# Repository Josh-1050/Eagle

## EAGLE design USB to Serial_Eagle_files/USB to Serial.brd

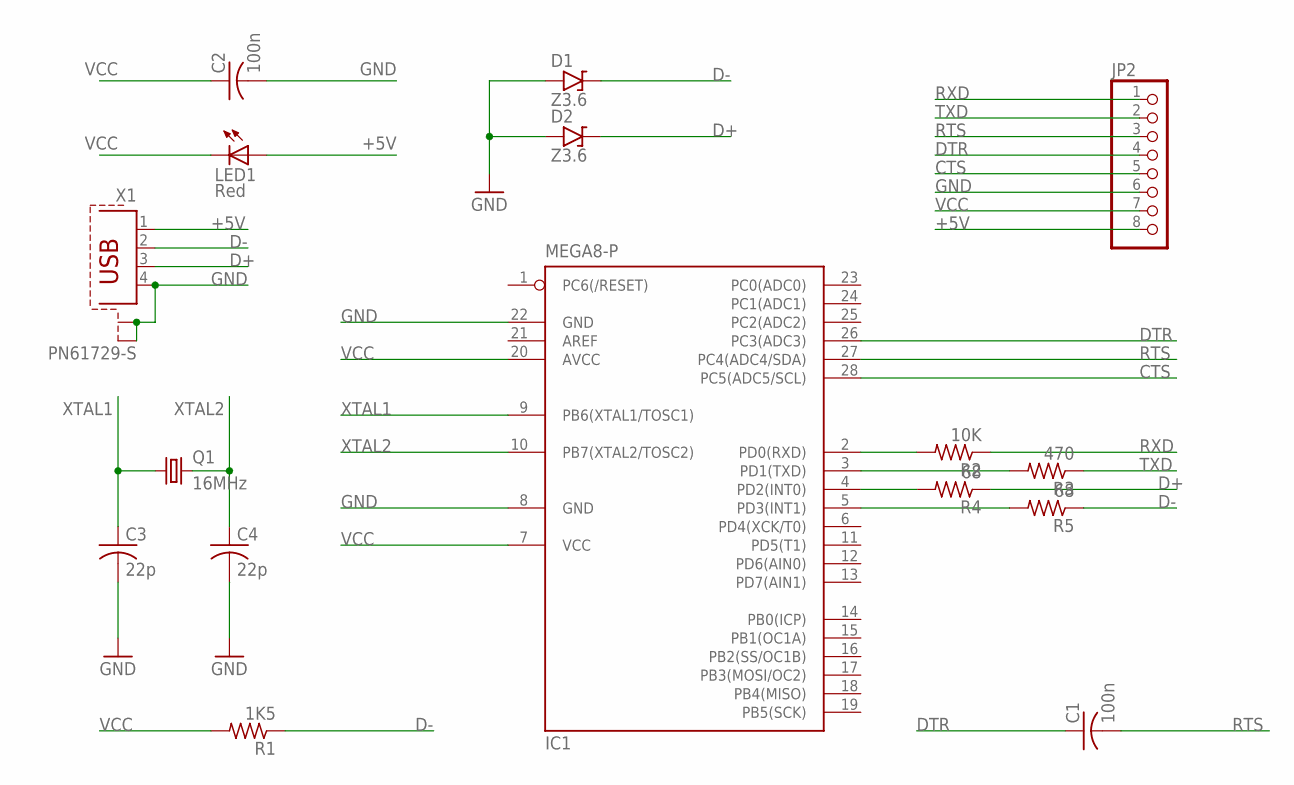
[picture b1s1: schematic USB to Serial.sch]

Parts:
C1, C2: 100n; C050-024X044
C3, C4: 22p; C050-024X044
D1, D2: Z3.6; DO35-3
IC1: MEGA8-P; DIL28-3
JP2: PINHD-1X8/90; 1X08/90
LED1: Red; LED3MM
Q1: 16MHz; HC49/S
R1: 1K5; 0207/7
R2: 10K; 0207/7
R3: 470; 0207/7
R4, R5: 68; 0207/7
X1: PN61729-S

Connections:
+5V: JP2.8, LED1.A, X1.1
CTS: IC1.28 (PC5(ADC5/SCL)), JP2.5
D+: D2.C, R4.1, X1.3
D-: D1.C, R1.1, R5.1, X1.2
DTR: C1.1, IC1.26 (PC3(ADC3)), JP2.4
GND: C2.2, C3.2, C4.2, D1.A, D2.A, IC1.8 (GND), IC1.22 (GND), JP2.6, X1.4, X1.S1, X1.S2
unnamed: IC1.2 (PD0(RXD)), R2.2
unnamed: IC1.3 (PD1(TXD)), R3.2
unnamed: IC1.4 (PD2(INT0)), R4.2
unnamed: IC1.5 (PD3(INT1)), R5.2
RTS: C1.2, IC1.27 (PC4(ADC4/SDA)), JP2.3
RXD: JP2.1, R2.1
TXD: JP2.2, R3.1
VCC: C2.1, IC1.7 (VCC), IC1.20 (AVCC), JP2.7, LED1.K (C), R1.2
XTAL1: C3.1, IC1.9 (PB6(XTAL1/TOSC1)), Q1.1
XTAL2: C4.1, IC1.10 (PB7(XTAL2/TOSC2)), Q1.2

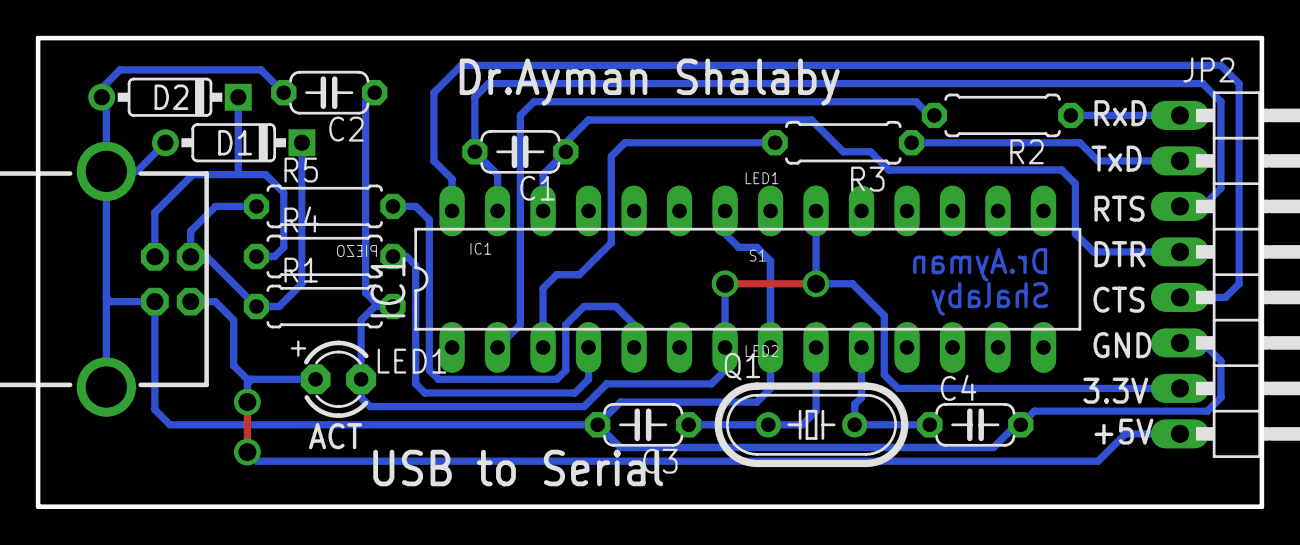
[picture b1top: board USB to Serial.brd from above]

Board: 2 copper layers, 68.3 x 26.2 mm, 16 parts (0 on the bottom side), 16 nets.

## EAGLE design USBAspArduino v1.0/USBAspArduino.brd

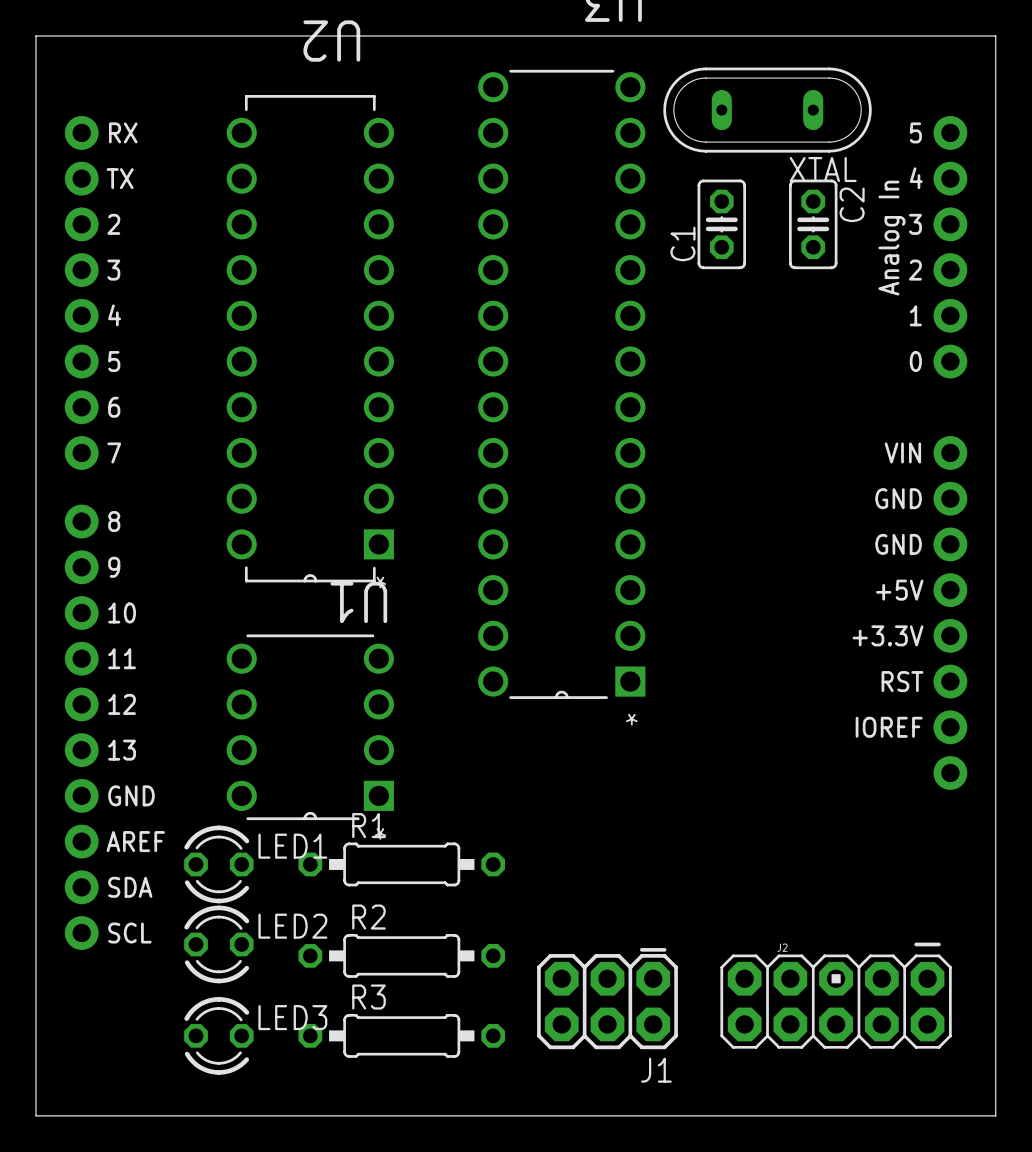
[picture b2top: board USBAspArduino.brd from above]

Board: 2 copper layers, 53.3 x 60.0 mm, 15 parts (0 on the bottom side), 13 nets, no tracks yet.

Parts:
C1, C2: 22pf; C025-025X050
J1: AVR_SPI_PRG_6PTH; 2X3
J2: AVR_SPI_PROG2PTH; AVR_ICSP
LED1: PROG; LED3MM
LED2: ERR; LED3MM
LED3: PULSE; LED3MM
R1, R2, R3: 1k; 0207/10
U1: ATTINY45-20PU; DIP254P762X533-8
U2: ATTINY2313V-10PU; DIP254P762X533-20
U3: ATMEGA328P-PU; DIP254P762X457-28
U$1: ARDUINO_R3_SHIELD; UNO_R3_SHIELD
XTAL: 16 MHZ; QS

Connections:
+5V: J1.2, J2.2, U1.8, U2.20, U3.7, U3.20, U$1.5V
GND: C1.1, C2.1, J1.6, J2.4, J2.6, J2.8, J2.10, R1.2, R2.2, R3.2, U1.4, U2.10, U3.8, U3.22, U$1.GND@0, U$1.GND@1, U$1.GND@2
MISO: J1.1, J2.9, U1.6, U2.18, U3.18, U$1.D12
MOSI: J1.4, J2.1, U1.5, U2.17, U3.17, U$1.D11
unnamed: LED1.A, U$1.D7
unnamed: LED2.A, U$1.D8
unnamed: LED3.A, U$1.D9
unnamed: LED1.K, R1.1
unnamed: LED2.K, R2.1
unnamed: LED3.K, R3.1
unnamed: C2.2, U3.10, XTAL.1
RESET: J1.5, J2.5, U1.1, U2.1, U3.1, U$1.D10
SCK: C1.2, J1.3, J2.7, U1.7, U2.19, U3.9, U3.19, U$1.D13, XTAL.2

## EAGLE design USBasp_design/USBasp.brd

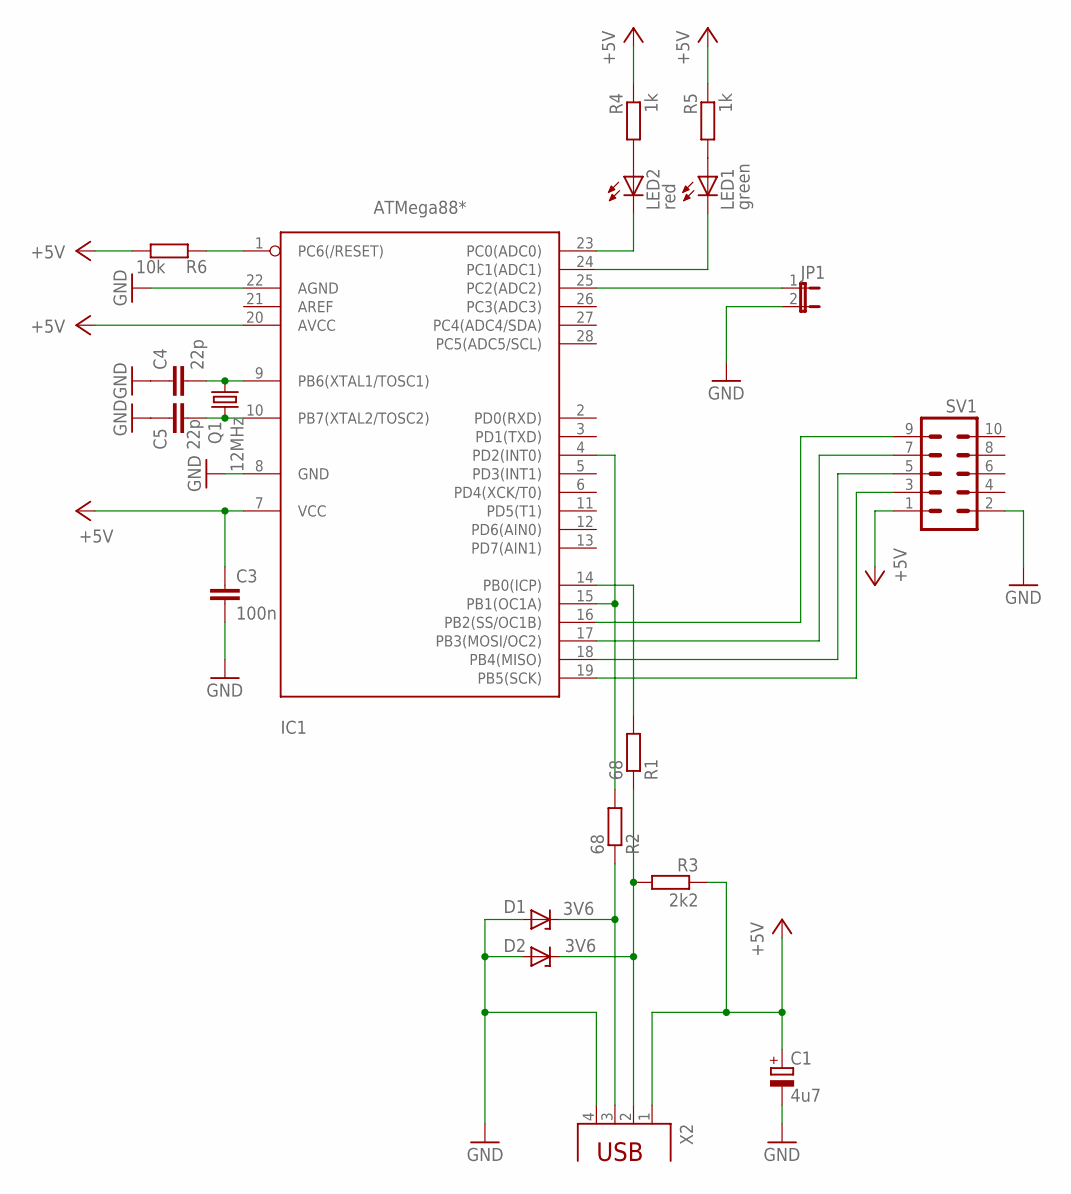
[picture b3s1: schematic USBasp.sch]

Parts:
C1: 4u7; E2,5-5
C3: 100n; C025-024X044
C4, C5: 22p; C025-024X044
D1, D2: 3V6; DO34Z7
IC1: ATMega88*; DIL28-3
JP1: JP1E; JP1
LED1: green; LED3MM
LED2: red; LED3MM
Q1: 12MHz; HC49/S
R1, R2: 68; 0207/10
R3: 2k2; 0207/10
R4, R5: 1k; 0207/10
R6: 10k; 0207/10
SV1: MA05-2
X2: PN87520

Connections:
+5V: C1.+, C3.1, IC1.7 (VCC), IC1.20 (AVCC), R3.1, R4.1, R5.1, R6.1, SV1.1, X2.1
GND: C1.-, C3.2, C4.1, C5.1, D1.A, D2.A, IC1.8 (GND), IC1.22 (AGND), JP1.2, SV1.2, X2.4
unnamed: IC1.25 (PC2(ADC2)), JP1.1
unnamed: IC1.19 (PB5(SCK)), SV1.3
unnamed: IC1.1 (PC6(/RESET)), R6.2
unnamed: IC1.18 (PB4(MISO)), SV1.5
unnamed: D2.C, R1.1, R3.2, X2.2
unnamed: IC1.17 (PB3(MOSI/OC2)), SV1.7
unnamed: IC1.4 (PD2(INT0)), IC1.15 (PB1(OC1A)), R2.2
unnamed: D1.C, R2.1, X2.3
unnamed: IC1.16 (PB2(SS/OC1B)), SV1.9
unnamed: LED2.A, R4.2
unnamed: IC1.23 (PC0(ADC0)), LED2.K (C)
unnamed: IC1.24 (PC1(ADC1)), LED1.K (C)
unnamed: IC1.14 (PB0(ICP)), R1.2
unnamed: C4.2, IC1.9 (PB6(XTAL1/TOSC1)), Q1.2
unnamed: C5.2, IC1.10 (PB7(XTAL2/TOSC2)), Q1.1
unnamed: LED1.A, R5.2

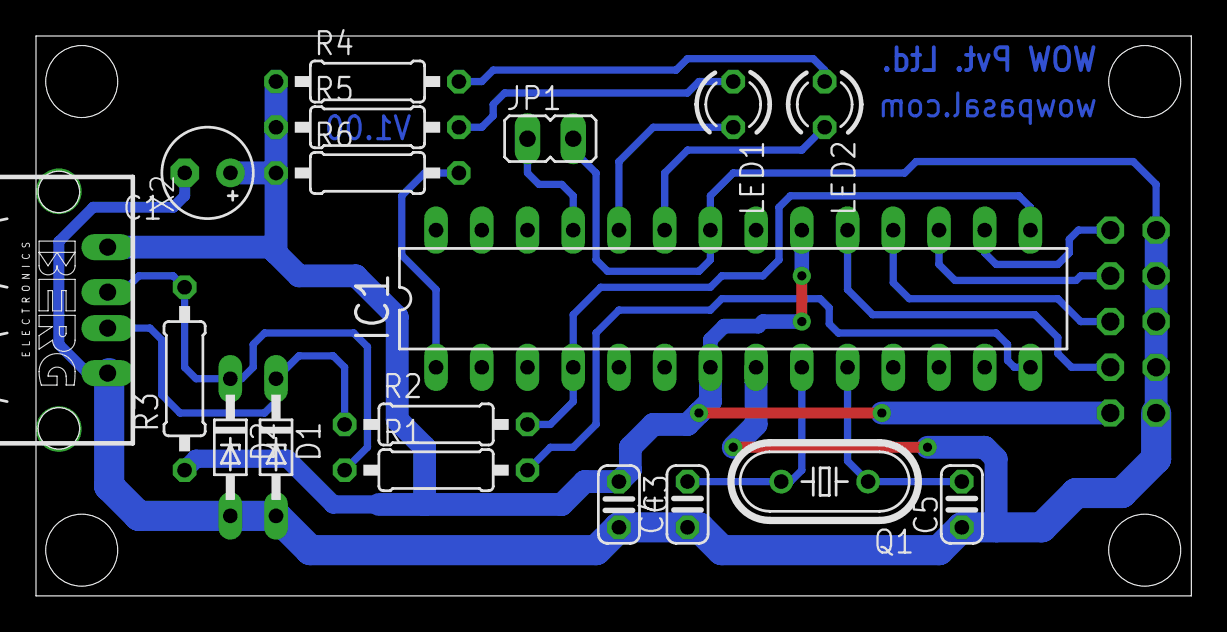
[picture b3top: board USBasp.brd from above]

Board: 2 copper layers, 64.2 x 31.1 mm, 19 parts (1 on the bottom side), 18 nets.

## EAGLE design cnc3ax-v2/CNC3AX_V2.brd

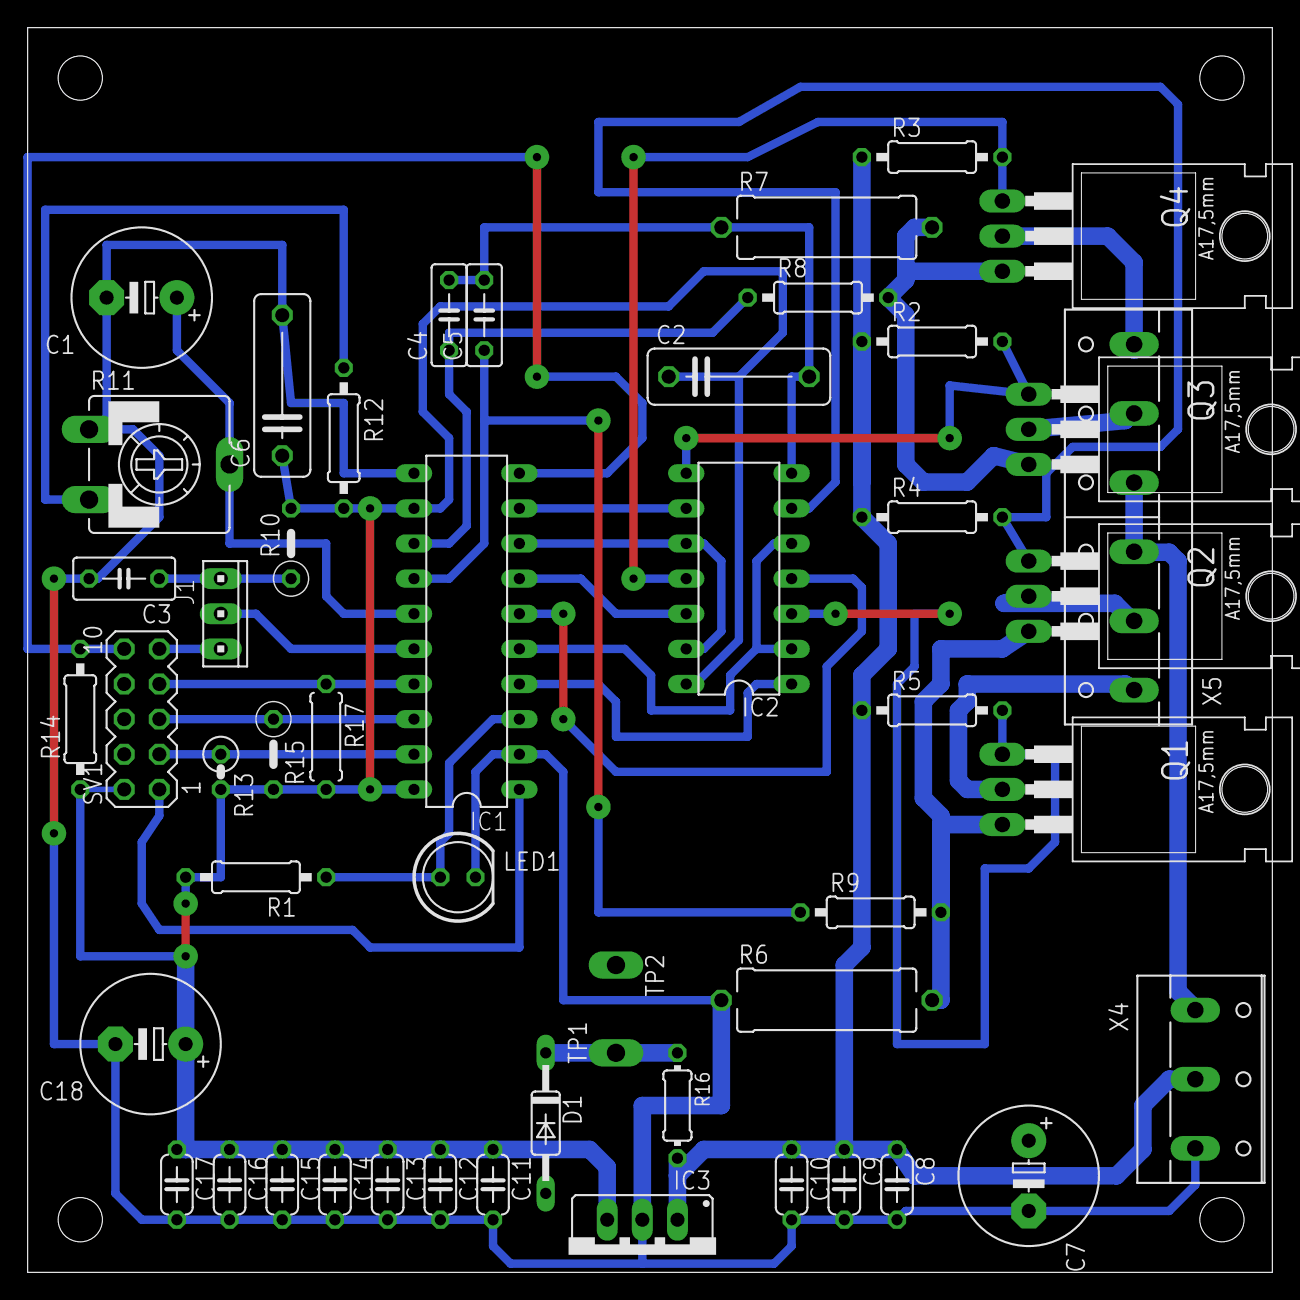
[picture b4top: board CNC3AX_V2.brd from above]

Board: 2 copper layers, 90.0 x 90.0 mm, 50 parts (0 on the bottom side), 34 nets.

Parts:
C1, C18: 330uF; E5-10,5
C2, C6: 100nF; C102-043X133
C3: 10nF; C050-030X075
C4, C5: 180pF; C050-025X075
C7: E5-10,5
C8, C9, C10, C11, C12, C13, C14, C15, C16, C17: 10nF; C050-024X044
D1: 1N4148; DO35-10
IC1: L297; DIL20
IC2: 74S09N; DIL14
IC3: 7805; 78XXS
J1: 10X03MTA
LED1: LED5MM
Q1, Q2, Q3, Q4: IRFZ44N; TO220
R1: 330; 0207/10
R2, R3, R4, R5: 3K3; 0207/10
R6, R7: 0,33/10W; P0613/15
R8, R9: 4k7; 0207/10
R10: 22K; 0207/5V
R11: CA9V
R12, R14: 4K7; 0207/10
R13: 4K7; 0207/2V
R15: 4K7; 0207/5V
R16: 0204/7
R17: 0207/7
SV1: MA05-2
TP1, TP2: PTR1PAD1-13Y; P1-13Y
X4: W237-103
X5: W237-136

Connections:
+18V: C8.1, C9.1, C10.1, IC3.IN, R2.1, R3.1, R4.1, R5.1, R16.2, X4.2
CLOCK: IC1.18, R15.1, SV1.5
CW/CCW: IC1.17, R17.1, SV1.7
ENABLE: IC1.10, R14.2, SV1.10
GND: C1.-, C2.2, C3.2, C4.2, C5.2, C6.2, C7.-, C8.2, C9.2, C10.2, C11.2, C12.2, C13.2, C14.2, C15.2, C16.2, C17.2, C18.-, D1.A, IC1.2, IC1.11, IC2.7, IC3.GND, LED1.K, R6.1, R7.1, R11.A, SV1.4, TP2.1, X4.3
H/F: IC1.19, R13.1, SV1.3
unnamed: IC1.4, IC2.1
unnamed: IC1.6, IC2.4
unnamed: IC1.7, IC2.12
unnamed: IC1.9, IC2.9
unnamed: IC1.5, IC2.2, IC2.5
unnamed: IC1.8, IC2.10, IC2.13
unnamed: D1.C, R16.1, TP1.1
unnamed: IC1.3, LED1.A, R1.1
unnamed: Q4.2, X5.6
unnamed: Q3.2, X5.5
unnamed: Q2.2, X5.2
unnamed: IC2.8, Q3.1, R2.2
unnamed: IC2.11, Q4.1, R3.2
unnamed: IC2.6, Q2.1, R4.2
unnamed: IC2.3, Q1.1, R5.2
unnamed: Q3.3, Q4.3, R7.2, R8.2
unnamed: Q1.3, Q2.3, R6.2, R9.2
unnamed: C5.1, IC1.14, R9.1
unnamed: C4.1, IC1.13, R8.1
unnamed: C3.1, J1.3, R10.1
unnamed: C1.+, IC1.15, R11.S
unnamed: IC1.16, J1.2
unnamed: R11.E, R12.1
unnamed: Q1.2, X5.1
SYNC_IN: J1.1, SV1.9
SYNC_OUT: IC1.1, SV1.1
VCC: C2.1, C6.1, C11.1, C12.1, C13.1, C14.1, C15.1, C16.1, C17.1, C18.+, IC1.12, IC1.20, IC2.14, IC3.OUT, R1.2, R10.2, R12.2, R13.2, R14.1, R15.2, R17.2, SV1.2
VMOTOR: C7.+, X4.1, X5.3, X5.4

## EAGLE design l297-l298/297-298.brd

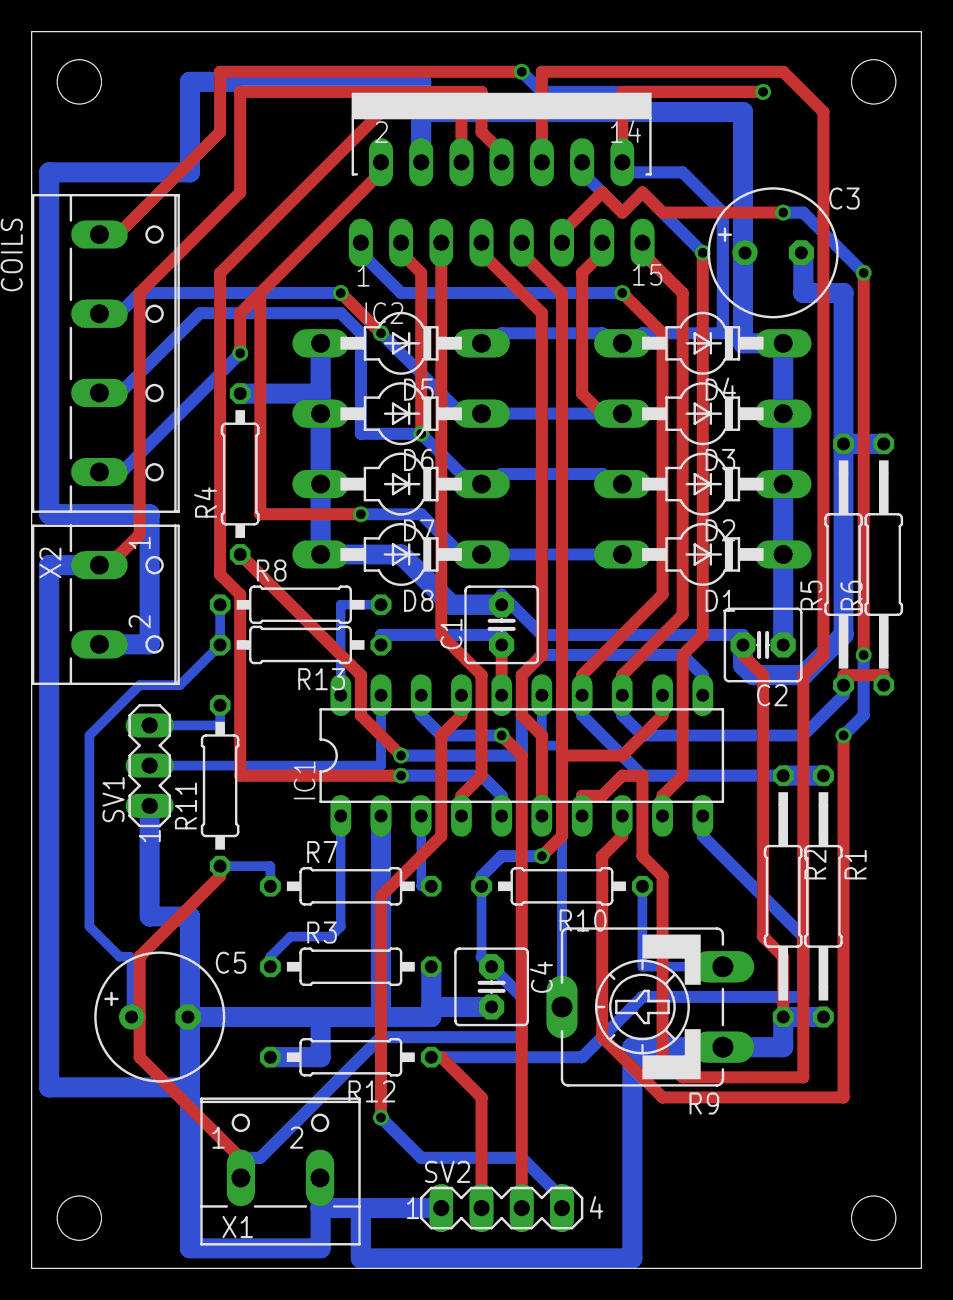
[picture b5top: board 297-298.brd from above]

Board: 2 copper layers, 56.2 x 78.1 mm, 33 parts (0 on the bottom side), 27 nets.

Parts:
C1: 3.3n; C2.5-5
C2, C4: .1u; C2.5-5
C3: 470uf; E3,5-8
C5: 100uf; E3,5-8
COILS: W237-4
D1, D2, D3, D4, D5, D6, D7, D8: BYV27; SOD57-10
IC1: L297; DIL20
IC2: L298; MULTIWATT-15
R1, R2, R5, R6: 1; 0207/15
R3, R4, R7, R8, R11: 10k; 0207/10
R9: 10K; CA9V
R10: 39K; 0207/10
R12: 47k; 0207/10
R13: 22k; 0207/10
SV1: MA03-1
SV2: MA04-1
X1: W237-102
X2: V+; W237-102

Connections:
+5V: C4.1, C5.+, IC1.12, IC2.9, R7.1, R8.1, R10.2, R11.1, R13.2, X1.1
GND: C1.2, C2.2, C3.-, C4.2, C5.-, D5.A, D6.A, D7.A, D8.A, IC1.2, IC2.8, R1.2, R2.2, R3.2, R4.2, R5.2, R6.2, R9.A, R12.2, SV1.1, SV2.1, X1.2, X2.1
unnamed: IC1.4, IC2.5
unnamed: IC1.6, IC2.7
unnamed: IC1.7, IC2.10
unnamed: IC1.9, IC2.12
unnamed: IC1.8, IC2.11
unnamed: IC1.5, IC2.6
unnamed: IC1.15, R9.S
unnamed: R9.E, R10.1
unnamed: COILS.4, D1.A, D8.C, IC2.2
unnamed: COILS.3, D2.A, D7.C, IC2.3
unnamed: COILS.2, D3.A, D6.C, IC2.13
unnamed: COILS.1, D4.A, D5.C, IC2.14
unnamed: IC1.13, IC2.15, R5.1, R6.1
unnamed: IC1.14, IC2.1, R1.1, R2.1
unnamed: IC1.1, R3.1
unnamed: IC1.19, SV1.2
unnamed: R11.2, SV1.3
unnamed: IC1.10, R12.1, SV2.2
unnamed: IC1.18, SV2.3
unnamed: IC1.17, SV2.4
unnamed: C1.1, IC1.16, R13.1
unnamed: IC1.11, R4.1
unnamed: IC1.3, R7.2
unnamed: C2.1, C3.+, D1.C, D2.C, D3.C, D4.C, IC2.4, X2.2
unnamed: IC1.20, R8.2

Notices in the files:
parts and their libraries:
SparkFun-Connectors: Licensing: Creative Commons ShareAlike 4.0 International - https://creativecommons.org/licenses/by-sa/4.0
